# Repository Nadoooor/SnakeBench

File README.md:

# SnakeBench
----------------

-----------------

## Description:

A snake-Styled Desktop Bench power supply, With adjustable Voltage, and fixed outputs, The project is Polished while working on the Panal Banana plugs places and shape. So every Snake, has its indication. 

## Why Iam Making this?

I have an old PC, and iam not using it anymore since i have another one. So, I decided to take components from it and convert them into Cool project. 

So, Iam starting with this one, Converting a PSU into a Cool Bench Power Supply that will help me with my Hardware Projects, and of course making it in a Snake-Style.

## Features:

- Banana Plugs for easy connect.
- Fixed Voltages came directly from the PSU.

    - +12V
    - +5V
    - 3v3

- Adjustable voltage plug with a digital screen to show the readings.
- Current limiting function.
- Fuse Box limiting the current to 10A.

## Photos: 

### Schematic:

### PCB:

### 3D PCB:

### 3D Assembly:

> [!NOTE]
> Here You Go the [Fusion Assembly Link](https://a360.co/4wditMu)

### How To Build:

1. Print all your parts.
2. Solder the Fuse Holders and the terminals to the PCB.
3. Add the Fuses to the Holders.
4. Get your PSU and install it inside the Case.
5. Rainforce it using the Screws from the back.
6. Add your PCB on its place in the Case.
7. Rainforce it using the Screws.
8. get 4 or 5 of each fixed voltage wires and connect them inside each terminal_Block. (For each Voltage Bus)
9. Take 3 or 4 wires of the Yellow wires (The 12V) and connect them to the input of the Voltage adjuster.
10. Connect the GND to the adjuster and to one Black Banana Plug to use it as the GND of the fixed voltage buses.
11. Connect the GND comming from the Adjuster to the one another Banana Plug to use it as the -Adj.
12. Connect also the +Out of the adjuster to one Red Banana Plug to use it as the +Adj.
13. Connect each Fixed Voltage bus to its banana Plug. 
    - Yellow --> +12V
    - Red --> +5V
    - Green --> 3v3
14. Rainforce all the Banana Plugs to the Front Panal. 
15. Rainforce the Adjuster to its place on top with its clips.
16. Take the other Color printed Front Panal Drawings, and rainforce them with super glue each on its place.
17. Do the same to Orphues on the right of the Back case.
18. Take the button, and connect one terminal of it to 1 GND wire from the PSU, and the other terminal connect to the Green wire coming from the PSU (PS-ON).
19. Rainforce it into the Panal using its clips.
20. Review all the connections and make sure nothing shorted. 
21. Close the front panal with M2 Screws with the back case. 
22. Becareful and plug it for first time and try it.
23. ENJOYYYY ;)

------------------------------

# Made with ❤️, By @Nadoooor

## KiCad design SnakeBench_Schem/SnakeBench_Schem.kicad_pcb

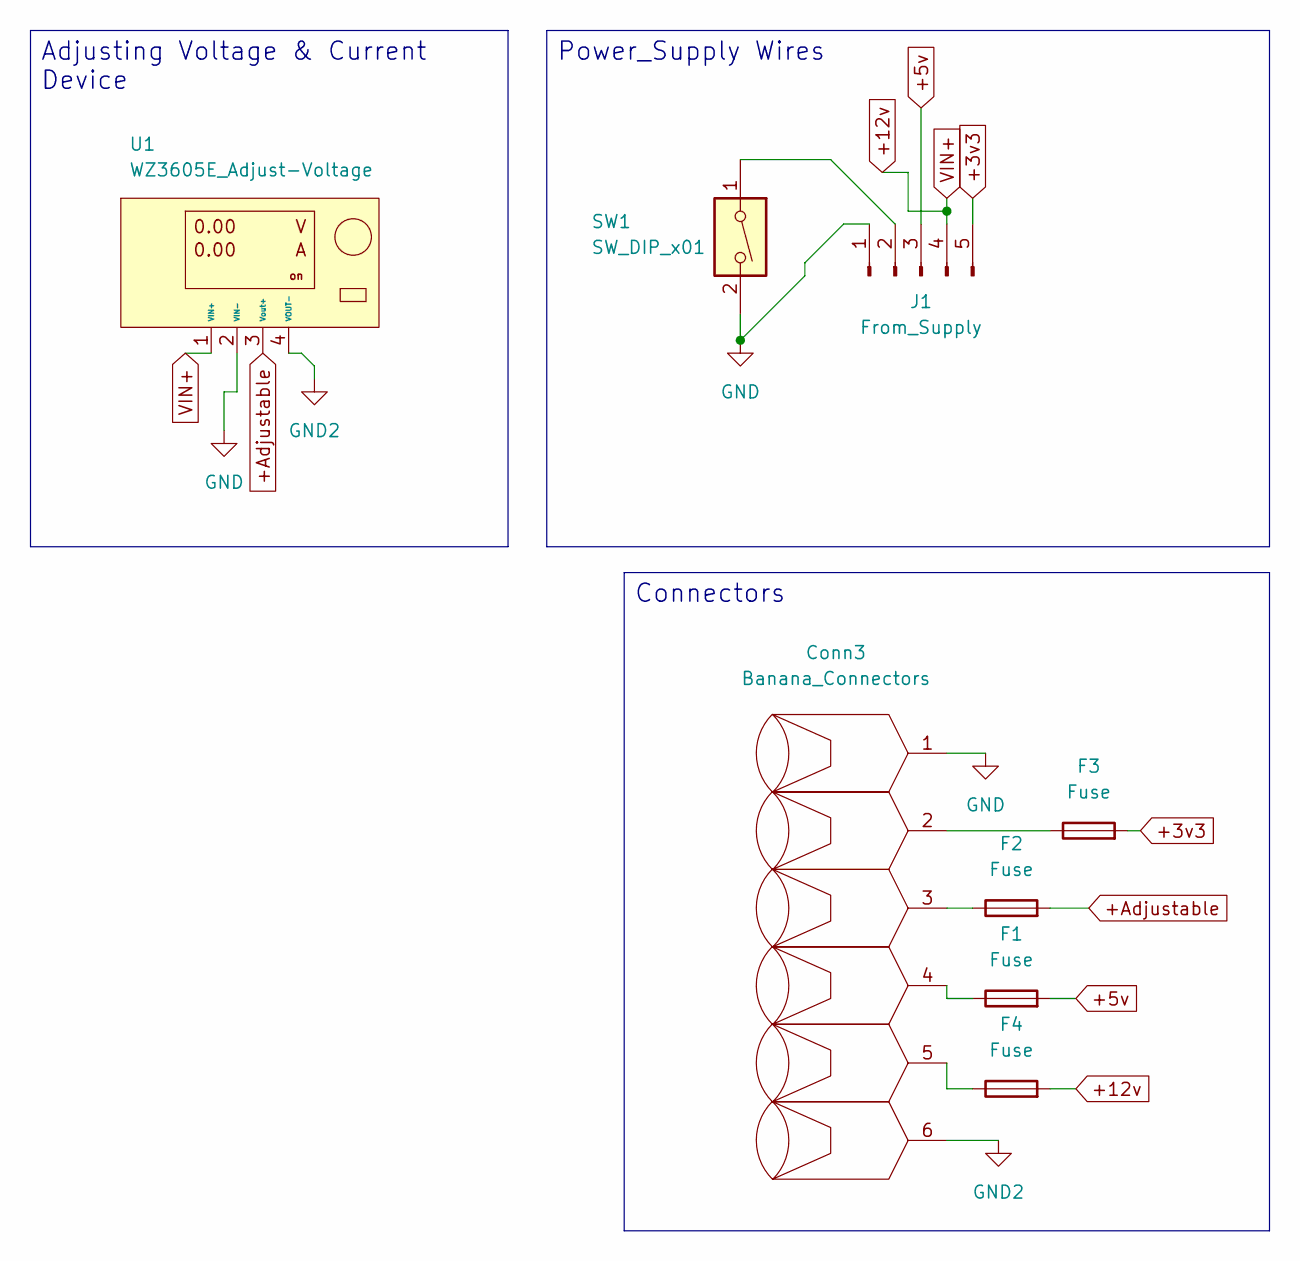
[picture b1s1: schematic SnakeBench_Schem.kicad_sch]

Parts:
Conn3: Banana_Connectors; Altech_AK100_1x06_P5.00mm
F1, F2, F3, F4: Fuse; Fuseholder_Cylinder-6.3x32mm_Schurter_0031-8002_Horizontal_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
J1: From_Supply; Altech_AK100_1x05_P5.00mm
SW1: SW_DIP_x01; Altech_AK100_1x02_P5.00mm
U1: WZ3605E_Adjust-Voltage; Altech_AK100_1x04_P5.00mm

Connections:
+3v3: F3.2, J1.5
+5v: F1.2, J1.3
+12v: F4.2, J1.4, U1.1 (VIN+)
+Adjustable: F2.2, U1.3 (Vout+)
GND: Conn3.1, J1.1, SW1.2, U1.2 (VIN-)
GND2: Conn3.6 (Pin_1), U1.4 (VOUT-)
unnamed: Conn3.2 (Pin_1), F3.1
unnamed: Conn3.3 (Pin_1), F2.1
unnamed: Conn3.4 (Pin_1), F1.1
unnamed: Conn3.5 (Pin_1), F4.1
unnamed: J1.2, SW1.1

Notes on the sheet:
Connectors
Adjusting Voltage & Current Device
Power_Supply Wires

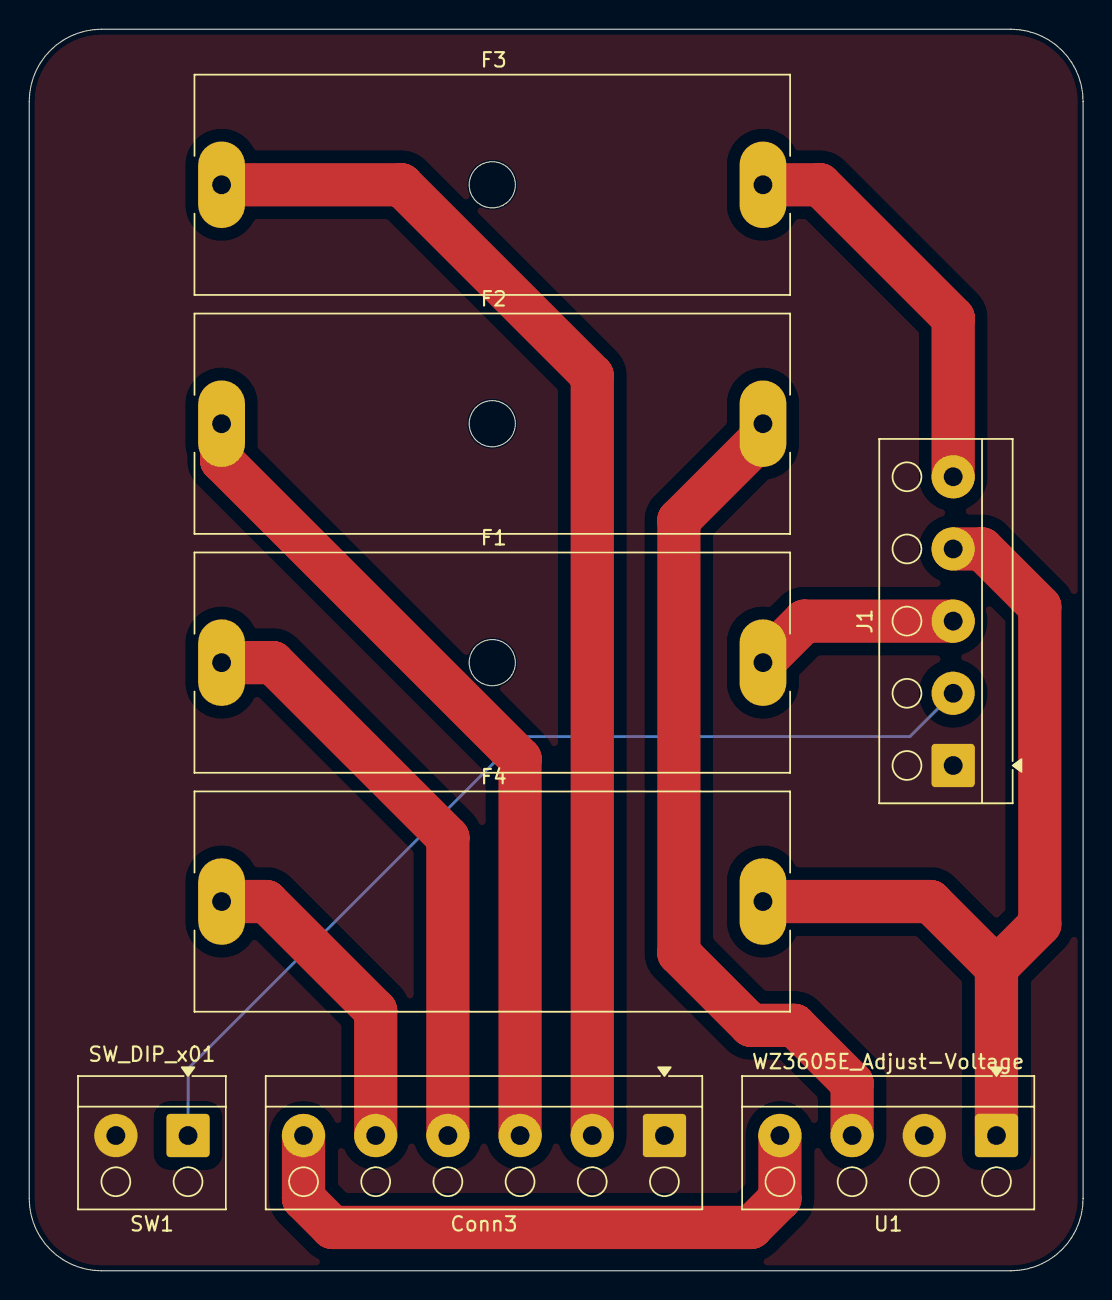
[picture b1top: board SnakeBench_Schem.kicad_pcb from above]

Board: 2 copper layers, 73.0 x 86.0 mm, 8 parts (0 on the bottom side), 11 nets.
